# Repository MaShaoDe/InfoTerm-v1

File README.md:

<!-- SPDX-License-Identifier: CC-BY-4.0 -->
<!-- Copyright (C) 2026 FerienBSD aka Marcel Sauder -->

# InfoTerm v1

Kleines Touch Terminal mit Zehnerblock: D1 mini (ESP8266), 2,8 Zoll Display mit Touch, Summer. Der Prototyp nimmt eine ID (4 Stellen) und eine PIN (6 bis 8 Stellen) entgegen, prüft nichts und spricht mit keinem Server. Er ist die neutrale Basis für Terminals aller Art (Herkunft: Arbeitszeit Terminal Firmware 0.11.0).

## Stand

Firmware 0.1.0 (Vorschlag): nicht kompiliert und nicht am Gerät getestet. Details: `STATUS.md`, `CHANGELOG.md`.

## Bedienung

- ID mit 4 Stellen eintippen, OK. PIN mit 6 bis 8 Stellen eintippen, OK. C löscht die letzte Ziffer, bei leerer PIN geht C zurück zur ID.
- **4 Sekunden aufs Display drücken**: Infoseite mit Version, Gerätename, WLAN, Signal, IP Adresse und freiem Speicher. Sie schliesst nach 15 Sekunden oder bei Berührung. Eine angefangene Eingabe wird dabei verworfen.
- Web Menü: IP Adresse der Infoseite im Browser öffnen (Benutzer `admin`, Passwort `gui_pass` aus `secrets.txt`, mindestens 8 Zeichen). Einstellbar: bis zu 3 WLAN Netze, Zeit bis Display aus, Gerätename, Passwort der Seite. Nach 5 falschen Eingaben ist die Seite bis zum Neustart gesperrt.
- Display aus nach 180 Sekunden ohne Eingabe (in `platformio.ini` für den Tischtest auf 20 gesetzt, im Web Menü einstellbar). Die weckende Berührung zählt nicht als Tastendruck.

## Hardware

Pinbelegung, Summer mit BC557 und 1,5 kΩ, Stückliste und offene Punkte für die Fertigung: `hardware/Spezifikation.md`.

## Bauen am Mac

```
cd ~/InfoTerm-v1
cp secrets.example.txt data/secrets.txt
open -e data/secrets.txt
pio run -t uploadfs -e d1_mini --upload-port /dev/cu.usbserial-A5069RR4
pio run -t upload -e d1_mini --upload-port /dev/cu.usbserial-A5069RR4
pio device monitor -b 115200 -p /dev/cu.usbserial-A5069RR4
```

`uploadfs` löscht den Speicher des Geräts, die Touch Kalibrierung (4 Ecken antippen) läuft danach einmal neu. Der D1 mini kann nur 2,4 GHz WLAN. Die USB Schnittstelle (`/dev/cu.usbserial-...`) mit `ls /dev/cu.*` prüfen.

## Lizenz

Firmware GPL-3.0-only, Hardware CERN-OHL-P-2.0, Dokumentation CC-BY-4.0. Copyright FerienBSD aka Marcel Sauder. Die Lizenztexte unter `LICENSES/` fehlen noch (offen).

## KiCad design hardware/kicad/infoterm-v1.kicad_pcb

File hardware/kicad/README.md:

<!-- SPDX-License-Identifier: CC-BY-4.0 -->
<!-- Copyright (C) 2026 FerienBSD aka Marcel Sauder -->

# InfoTerm v1: Schaltplan (KiCad)

Stand 24.11.2026. Vorschlag, offen: `infoterm-v1.kicad_sch` wurde als Text geschrieben und nie in KiCad geöffnet oder geprüft (kein ERC). Beim Öffnen können Fehler auftreten. Schaltung nach `hardware/Spezifikation.md`.

Hardware: CERN-OHL-P-2.0.

## Bauteile (Vorschlag, Muster ab 5 Stück)

| Ref | Teil | Footprint (Vorschlag) |
|---|---|---|
| J1, J2 | Buchsenleiste 1x8, 2,54 mm, für D1 mini (Reihenabstand 22,86 mm: offen, am Board messen) | PinSocket_1x08 |
| J3 | Buchsenleiste 1x14 für Display MSP2807 | PinSocket_1x14 |
| Q1 | BC557 (PNP), Beinchen C, B, E im Datenblatt prüfen | TO-92 |
| R1 | 1,5 kΩ | Axial DIN0207 |
| J4 | Pfostenstecker 1x2 für Summer | PinHeader_1x02 |
| J5 | USB-C Buchse, nur Strom (16 Pin SMD, z.B. HRO TYPE-C-31-M-12), am Gehäuserand | USB_C_Receptacle_HRO_TYPE-C-31-M-12 |
| R2, R3 | 5,1 kΩ an CC1 und CC2 gegen GND (nötig, sonst liefert ein USB-C Netzteil keine 5 V) | R_0805 |
| F1 | rückstellende Sicherung (Polyfuse) 1 A, Wert: offen | Fuse_1206 |
| C1, C2 | 220 µF Elko und 100 nF Keramik, 5 V gegen GND | CP_Radial_D6.3mm, C_0805 |

## Layout (Entwurf, offen)

`infoterm-v1.kicad_pcb`: 71,12 x 63,5 mm, 2 Lagen, Leiterbahn 0,3 mm (Strom 0,5 mm), Via 0,8 / 0,4 mm, GND Fläche auf beiden Lagen, 4 Löcher M3 (3,81 mm vom Rand), 7 Testpunkte rechts (TP1 SCK, TP2 MOSI, TP3 3V3, TP4 5V, TP5 VBUS_RAW, TP6 und TP7 GND), Silkscreen mit Titel, D1 mini Umriss (ESP8266, USB rechts), Beschriftung J3 und Rückseite (Copyright, Version, Repo). D1 mini gedreht: Antenne links mit rund 4,5 mm Abstand zur Kante, USB Ende rechts. Von der Kante bis unter die Antenne kein Kupfer (Annahme, offen: Lage mit echtem D1 mini auf einem 1:1 Ausdruck prüfen). Footprints aus der KiCad Bibliothek, Routing mit eigenem Skript. Eigene Abstands und Verbindungsprüfung ohne Befund, das ersetzt keinen DRC (DRC in KiCad offen).

Annahmen (offen):
- Display Modul steckt in J3 und ragt über den oberen Rand hinaus, D1 mini liegt mit dem USB Ende links. Pin 1 von J3 ist VCC: Seite am Modul prüfen.
- J5 (HRO TYPE-C-31-M-12) steht bündig an der unteren Kante, Schnittstelle zum Gehäuse (Schlitz) offen.
- Vor dem DRC alle Zonen füllen (Taste B).

## Offen

- Layout und Gerber fehlen.
- Strom von Summer und Hintergrundlicht (D0 direkt) nicht gemessen.
- Stromversorgung (Vorschlag): USB-C Buchse J5 auf dem PCB speist den 5V Pin des D1 mini. Netzteil: 5 V, Strom nicht gemessen.
- D1 mini nie gleichzeitig über seine eigene USB Buchse und J5 speisen, bevor geklärt ist, ob der Klon eine Diode am 5V Pin hat (offen).
- Symbol J5 nutzt jetzt die Original Pad Namen (A1, A4, A5, A9, A12, B1, B4, B5, B9, B12, SH).
- Buchse hat 0,5 mm Raster: Handlöten ohne Mikroskop heikel, Fertiger Bestückung oder grössere Buchse prüfen (offen).
- Gehäuse: PCB am Rand verschrauben, Schlitz für die Buchse einplanen (offen).

- J3 (Display): JST XH B14B-XH-A, 14 polig, 2,5 mm Raster (nicht 2,54), senkrecht. Kabel: XH Buchse 14P Single Head, 200 mm, 22 AWG, anderes Ende am Display angelötet (Stiftleiste dort auslöten). Raster der Stiftleiste vor der Bestellung mit 32,5 mm von Pin 1 bis Pin 14 prüfen (offen).
- J4 (Buzzer): Schraubklemme KF350-2P, 3,5 mm Raster, Kabeleingang nach rechts. Footprint nach Datenblatt (Gehäuse rund 7,5 x 8,8 mm, Draht 24 bis 18 AWG), Bohrung 1,2 mm angenommen (Stiftdurchmesser steht nicht im Datenblatt, offen: an der gelieferten Klemme messen).

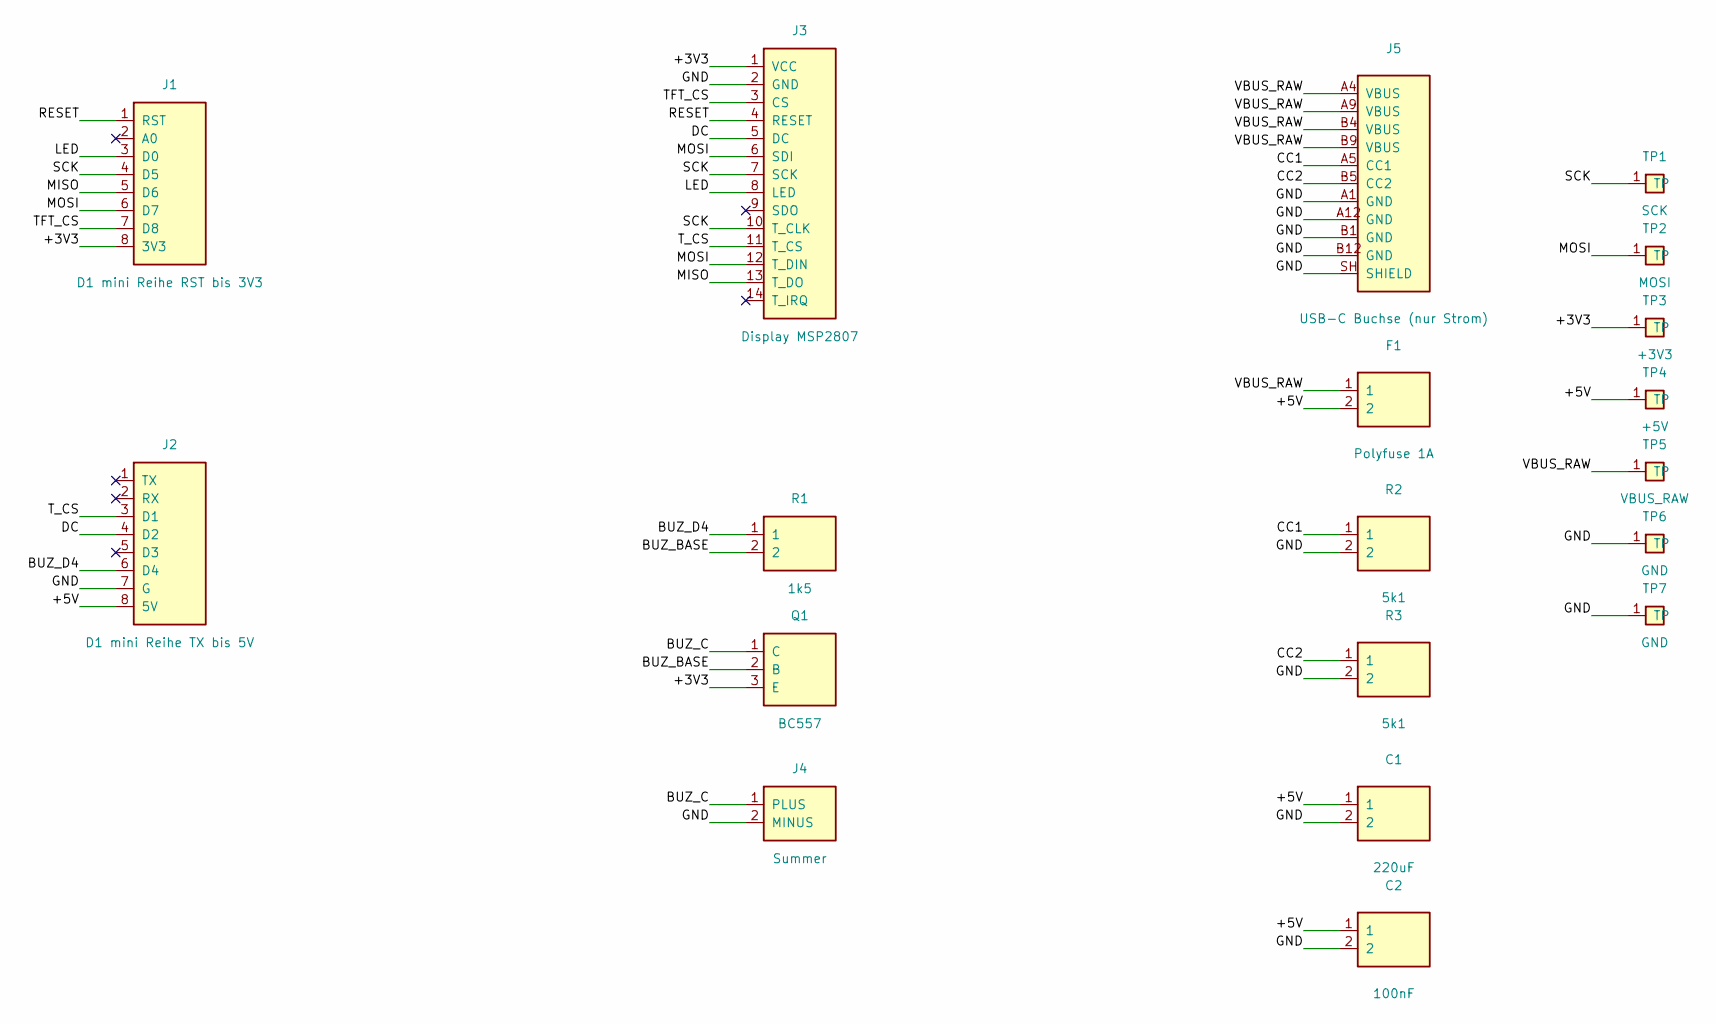
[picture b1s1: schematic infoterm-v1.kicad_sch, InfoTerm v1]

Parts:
C1: 220uF; CP_Radial_D6.3mm_P2.50mm
C2: 100nF; C_0805_2012Metric
F1: Polyfuse 1A; Fuse_1206_3216Metric
J1: D1 mini Reihe RST bis 3V3; PinSocket_1x08_P2.54mm_Vertical
J2: D1 mini Reihe TX bis 5V; PinSocket_1x08_P2.54mm_Vertical
J3: Display MSP2807; JST_XH_B14B-XH-A_1x14_P2.50mm_Vertical
J4: Summer; TerminalBlock_Phoenix_PT-1,5-2-3.5-H_1x02_P3.50mm_Horizontal
J5: USB-C Buchse (nur Strom); USB_C_Receptacle_HRO_TYPE-C-31-M-12
Q1: BC557; TO-92_Inline
R1: 1k5; R_Axial_DIN0207_L6.3mm_D2.5mm_P10.16mm_Horizontal
R2, R3: 5k1; R_0805_2012Metric
TP1: SCK; TestPoint_THTPad_D1.5mm_Drill0.7mm
TP2: MOSI; TestPoint_THTPad_D1.5mm_Drill0.7mm
TP3: +3V3; TestPoint_THTPad_D1.5mm_Drill0.7mm
TP4: +5V; TestPoint_THTPad_D1.5mm_Drill0.7mm
TP5: VBUS_RAW; TestPoint_THTPad_D1.5mm_Drill0.7mm
TP6, TP7: GND; TestPoint_THTPad_D1.5mm_Drill0.7mm

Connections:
/+3V3: J1.8 (3V3), J3.1 (VCC), Q1.3 (E), TP3.1
/+5V: C1.1, C2.1, F1.2, J2.8 (5V), TP4.1
/BUZ_BASE: Q1.2 (B), R1.2
/BUZ_C: J4.1 (PLUS), Q1.1 (C)
/BUZ_D4: J2.6 (D4), R1.1
/CC1: J5.A5 (CC1), R2.1
/CC2: J5.B5 (CC2), R3.1
/DC: J2.4 (D2), J3.5 (DC)
/GND: C1.2, C2.2, J2.7 (G), J3.2 (GND), J4.2 (MINUS), J5.A1 (GND), J5.A12 (GND), J5.B1 (GND), J5.B12 (GND), J5.SH (SHIELD), R2.2, R3.2, TP6.1, TP7.1
/LED: J1.3 (D0), J3.8 (LED)
/MISO: J1.5 (D6), J3.13 (T_DO)
/MOSI: J1.6 (D7), J3.6 (SDI), J3.12 (T_DIN), TP2.1
/RESET: J1.1 (RST), J3.4 (RESET)
/SCK: J1.4 (D5), J3.7 (SCK), J3.10 (T_CLK), TP1.1
/TFT_CS: J1.7 (D8), J3.3 (CS)
/T_CS: J2.3 (D1), J3.11 (T_CS)
/VBUS_RAW: F1.1, J5.A4 (VBUS), J5.A9 (VBUS), J5.B4 (VBUS), J5.B9 (VBUS), TP5.1

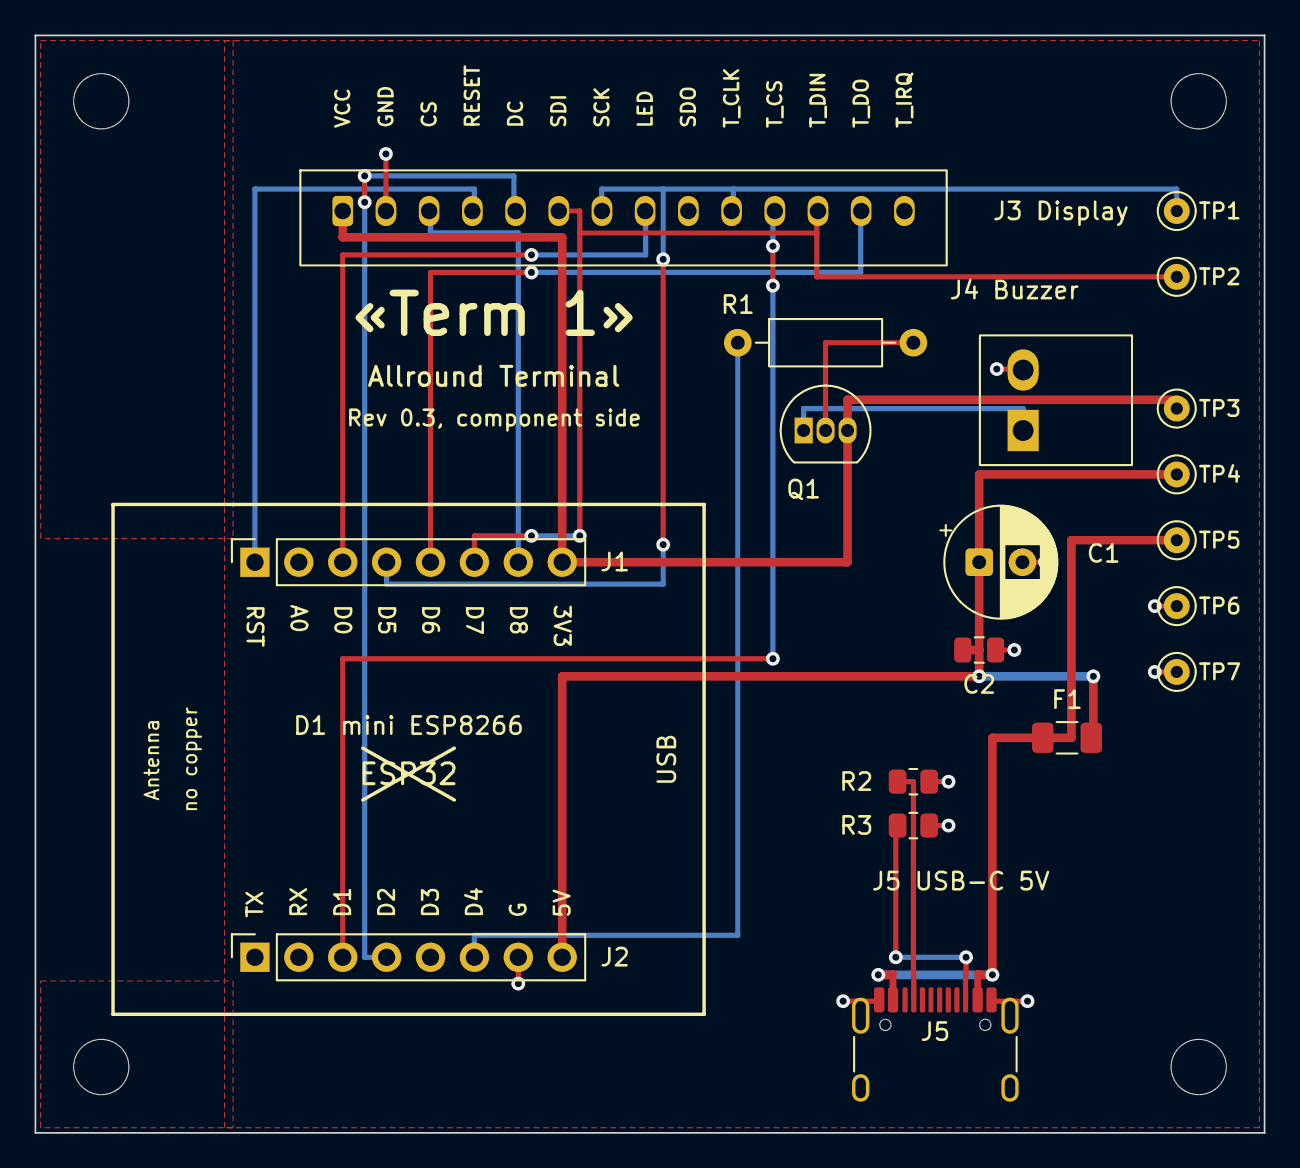
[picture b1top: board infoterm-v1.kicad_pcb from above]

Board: 2 copper layers, 71.1 x 63.5 mm, 23 parts (0 on the bottom side), 17 nets.

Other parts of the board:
H: M3; MountingHole_3.2mm_M3
H#2, H#3, H#4: M3; MountingHole_3.2mm_M3

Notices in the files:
hardware/kicad/infoterm-v1.kicad_pcb:
SPDX-License-Identifier: CERN-OHL-P-2.0
